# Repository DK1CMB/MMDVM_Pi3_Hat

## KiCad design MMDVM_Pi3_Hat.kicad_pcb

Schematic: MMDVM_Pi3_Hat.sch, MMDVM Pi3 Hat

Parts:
C1, C4, C7, C9, C10, C14, C17, C19, C27, C32: 100n; C_0805_2012Metric
C2, C3, C5: 10u/10V; CP_EIA-6032-15_Kemet-U
C6: 10u; C_0805_2012Metric
C8: 1n; C_0805_2012Metric
C11, C16, C20, C28, C31: 10n; C_0805_2012Metric
C12: 470p; C_0805_2012Metric
C13: 15n; C_0805_2012Metric
C15: 22p; C_0805_2012Metric
C18: 22n; C_0805_2012Metric
C21: 220p; C_0805_2012Metric
C22, C29, C30: 6p8; C_0805_2012Metric
C23, C24: 20p; C_0805_2012Metric
C25: 10p; C_0805_2012Metric
C26: 4p7; C_0805_2012Metric
D1, D4, D8: red; LED_0805_2012Metric
D2, D5: green; LED_0805_2012Metric
D3, D6: yellow; LED_0805_2012Metric
D7: amber; LED_0805_2012Metric
D9: blue; LED_0805_2012Metric
J1: USB_B_Mini; USB_Micro-B_Wuerth_629105150521
J2: I2C; PinHeader_1x04_P2.54mm_Vertical
J3: STLink; PinHeader_1x04_P2.54mm_Vertical
J4: Display; PinHeader_1x04_P2.54mm_Vertical
J5: SMA; RF_SMA_Vertical_5-1814832-1; MPN 5-1814832-1; Digi-Key_PN A97594-ND
J6: Conn_02x10_Counter_Clockwise; PinHeader_2x10_P2.54mm_Vertical
L1: 10u; L_0805_2012Metric
L2: 18n; L_0805_2012Metric
L3, L4: 22n; L_0805_2012Metric
L5: 20n; L_0805_2012Metric
L6: 27n; L_0805_2012Metric
MK1, MK2, MK3, MK4: M2.5; MountingHole_2.7mm_M2.5
P1: Pi3; PinSocket_2x20_P2.54mm_Vertical
R1, R4, R6: 20; R_0805_2012Metric
R2, R11: 10k; R_0805_2012Metric
R3, R5, R7, R8, R9, R10, R12, R13, R14, R18, R19, R20: 1k; R_0805_2012Metric
R15: 560; R_0805_2012Metric
R16: 270; R_0805_2012Metric
R17: 3r9; R_0805_2012Metric
R21: 1k1; R_0805_2012Metric
R22: 3k8; R_0805_2012Metric
S1: B3F-1000; Switch_Tactile_THT_B3F-1xxx; MPN B3F-1000; Digi-Key_PN SW400-ND
U1: LM1117MPX-3.3; SOT-223; MPN LM1117MPX-3.3/NOPB; Digi-Key_PN LM1117MPX-3.3/NOPBCT-ND
U2: STM32F103C8T6; LQFP-48_7x7mm_P0.5mm
U3: ADF7021; QFN-48-7x7mm_P0.5_EP4.25
U4: OSHW-Logo_19x20mm; OSHW-Logo_19x20mm_SilkScreen
U5: MMDVM-Logo; LOGO
U6: KiCAD-Logo_6mm; KiCad-Logo2_6mm_SilkScreen
U7: CC_BY_NC_SA; Logo_silk_CC-BY-NC-SA_10x3.6mm
X1: ECS-TXO-5032-147.4-TR; Crystal_SMD_5032-4Pin_5.0x3.2mm; Digikey_Bestellnummer XC2067CT-ND
Y1: 8MHz; Crystal_SMD_5032-2Pin_5.0x3.2mm
txt1: PartName; MMDVM_Pi3_Hat

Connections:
+3V3: C5.1, C6.1, C9.2, C10.2, C11.1, C14.2, C16.1, C20.1, C21.1, C22.1, C28.1, C31.1, J2.1, J3.1, J6.2, L1.2, L3.2, P1.1, P1.17, R2.2, R3.2, R5.2, U2.1, U2.9, U2.24, U2.36, U2.48, U3.3, U3.9, U3.32, U3.40, U3.43, X1.4
+5V: C2.1, J1.1 (VBUS), J4.1, J6.1, P1.2, P1.4, R1.2, U1.3
/GPIO4(GCLK): P1.7
/GPIO5: P1.29
/GPIO6: P1.31
/GPIO7(SPI1_CE_N): P1.26
/GPIO8(SPI0_CE_N): P1.24
/GPIO9(SPI0_MISO): P1.21
/GPIO10(SPI0_MOSI): P1.19
/GPIO11(SPI0_SCK): P1.23
/GPIO12(PWM0): P1.32
/GPIO13(PWM1): P1.33
/GPIO16: P1.36
/GPIO17(GEN0): P1.11
/GPIO18(GEN1)(PWM0): P1.12
/GPIO19(SPI1_MISO): P1.35
/GPIO20(SPI1_MOSI): P1.38, R11.2
/GPIO22(GEN3): P1.15
/GPIO23(GEN4): P1.16
/GPIO24(GEN5): P1.18
/GPIO25(GEN6): P1.22
/GPIO26: P1.37
/GPIO27(GEN2): P1.13
/ID_SC: P1.28
/ID_SD: P1.27
BOOT0: R11.1, U2.44
CE: U2.3, U3.24
CLK_OUT: J6.3, J6.12, R18.1, U2.38
COS_LED: R7.2, U2.28
DATA_IN: J6.5, R19.1, U2.39
DATA_OUT: J6.4, R20.1, U2.40
DISP_RXD: J4.2, U2.13
DISP_TXD: J4.3, U2.12
DMR_LED: R10.2, U2.26
DSTAR_LED: R9.2, U2.25
GND: C1.2, C2.2, C3.2, C4.2, C5.2, C6.2, C8.2, C9.1, C10.1, C11.2, C12.2, C13.2, C14.1, C16.2, C17.2, C19.1, C20.2, C21.2, C22.2, C23.2, C24.2, C27.1, C28.2, C29.2, C30.2, C31.2, C32.2, D2.1, D3.1, D4.1, D5.1, D6.1, D7.1, D8.1, D9.1, J1.4 (ID), J1.5 (GND), J1.6 (Shield), J2.2, J3.4, J4.4, J5.1, J6.10, J6.11, P1.6, P1.9, P1.14, P1.20, P1.25, P1.30, P1.34, P1.39, R21.1, R22.1, S1.3, S1.4, U1.1, U2.8, U2.20, U2.23, U2.35, U2.47, U3.5, U3.12, U3.19, U3.22, U3.29, U3.45, U3.47, U3.49, X1.2
NRST: C1.1, P1.40, R2.1, S1.1, S1.2, U2.7
NXDN_LED: R14.2, U2.29
unnamed: C3.1, C4.1, L1.1, U1.2, U1.4
unnamed: C7.1, L4.1
unnamed: C7.2, J5.2
unnamed: C8.1, R15.2, R16.2, U3.42
unnamed: C12.1, R15.1, U3.1
unnamed: C13.1, R16.1
unnamed: C15.1, X1.3
unnamed: C15.2, U3.39
unnamed: C17.1, R17.1
unnamed: C18.1, U3.48
unnamed: C18.2, R17.2, U3.2
unnamed: C19.2, U3.41
unnamed: C23.1, U2.5, Y1.1
unnamed: C24.1, U2.6, Y1.2
unnamed: C25.1, L3.1, U3.4
unnamed: C25.2, C26.2, L5.2
unnamed: C26.1, L6.2, U3.6
unnamed: C27.2, U3.31
unnamed: C29.1, L4.2, L5.1
unnamed: C30.1, L6.1, U3.7
unnamed: C32.1, U3.11
unnamed: D1.2, R3.1
unnamed: D2.2, R5.1
unnamed: D3.2, R7.1
unnamed: D4.2, R8.1
unnamed: D5.2, R9.1
unnamed: D6.2, R10.1
unnamed: D7.2, R12.1
unnamed: D8.2, R13.1
unnamed: D9.2, R14.1
unnamed: J1.2 (D-), R6.2
unnamed: J1.3 (D+), R4.2
unnamed: L2.1, U3.46
unnamed: L2.2, U3.44
unnamed: R18.2, U3.36
unnamed: R19.2, U3.35
unnamed: R20.2, U3.34
unnamed: R21.2, U3.8
unnamed: R22.2, U3.10
P25_LED: R13.2, U2.18
PTT_LED: R8.2, U2.27
RXD: J6.18, P1.8, U2.31
SCL: J2.3, J6.19, P1.5
SDA: J2.4, J6.20, P1.3
SERVICE: D1.1, U2.2
SLE: J6.9, U2.45, U3.25
SW_CLK: J3.3, J6.13, U2.37
SW_DIO: J3.2, J6.14, U2.34
S_CLK: J6.6, U2.41, U3.28
S_DATA: J6.8, U2.42, U3.26
S_READ: J6.7, U2.43, U3.27
TXD: J6.17, P1.10, U2.30
USB_DM: J6.16, R1.1, R4.1, U2.32
USB_DP: J6.15, R6.1, U2.33
YSF_LED: R12.2, U2.19

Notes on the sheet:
Mounting Holes
Raspberry Pi 3 Connector
USB-Connection
Reset
Power supply and filtering
Status-LED
Connectors
Testpoints
Text & Logo

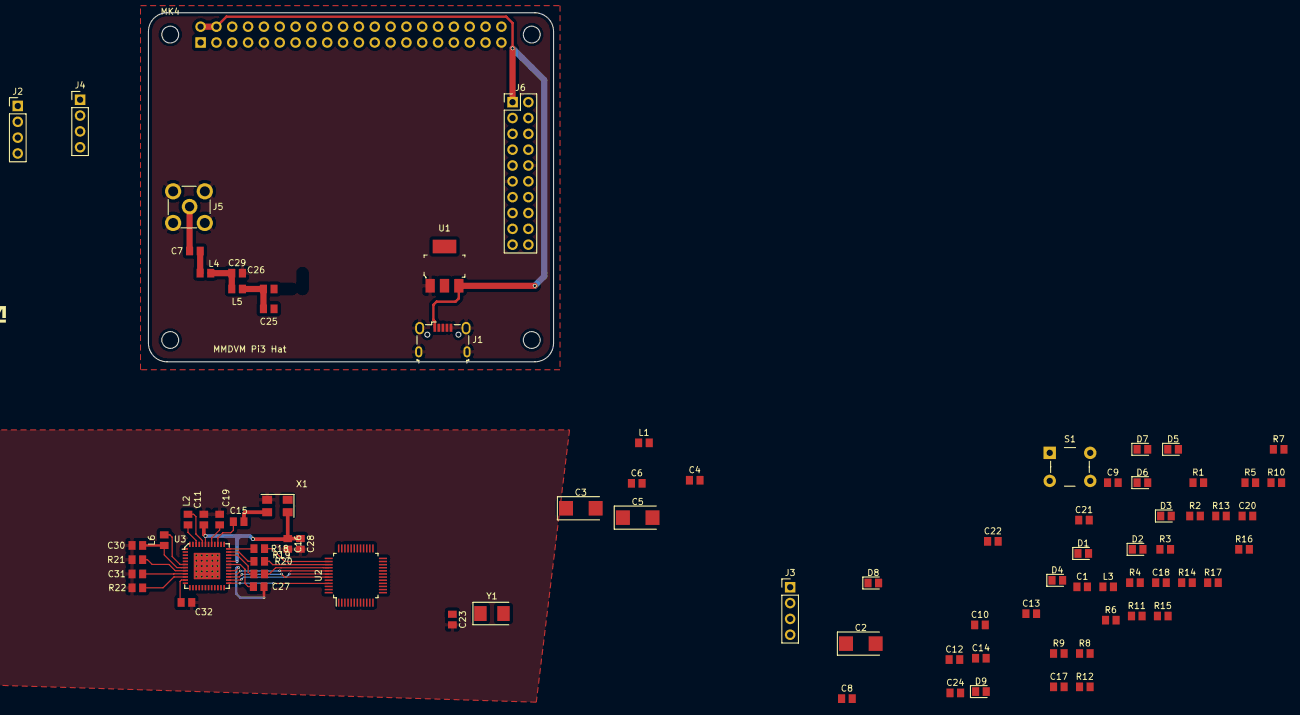
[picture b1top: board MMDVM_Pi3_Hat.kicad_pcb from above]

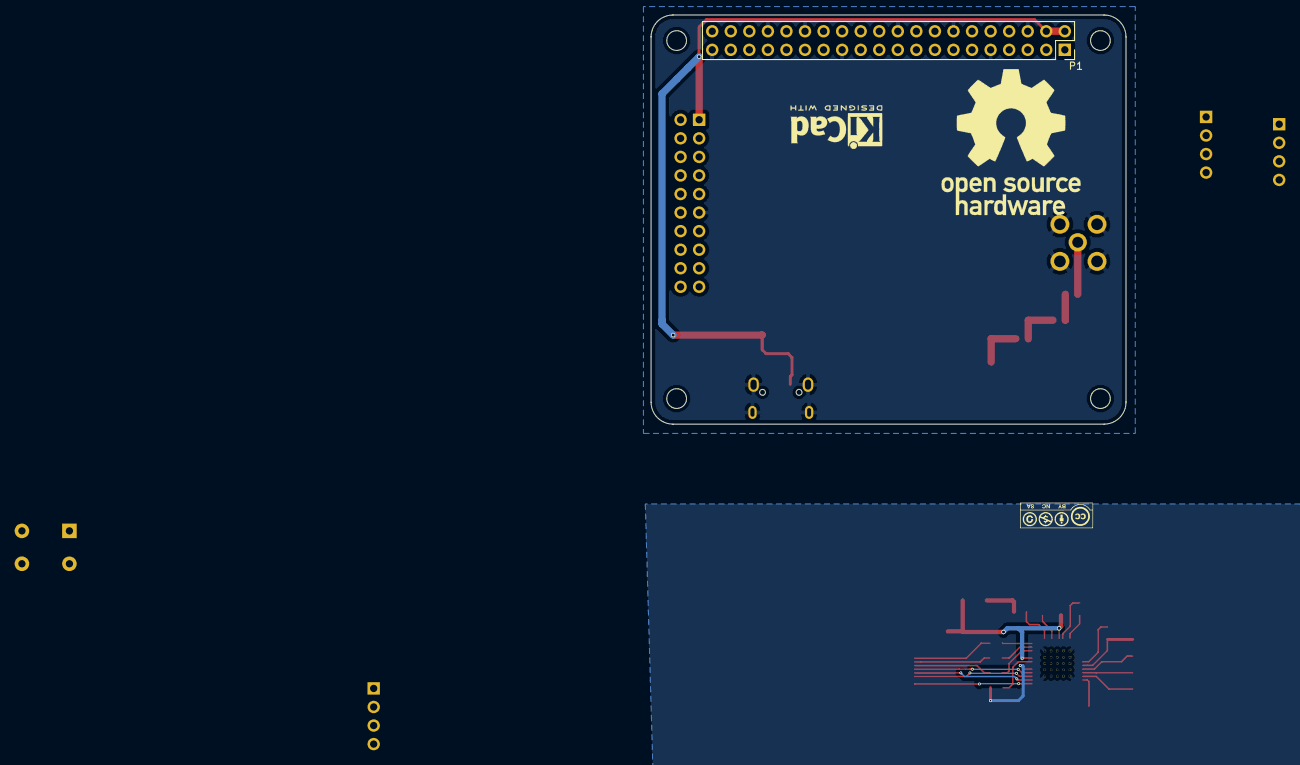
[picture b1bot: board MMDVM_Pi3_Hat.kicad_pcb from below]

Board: 2 copper layers, 65.0 x 56.0 mm, 91 parts (4 on the bottom side), 71 nets.

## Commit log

2018-06-13 Libs moved
2018-06-13 Start PCB Layout
2018-06-16 Save
